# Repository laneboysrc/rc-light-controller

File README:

This project is for a light controller for Radio Controlled cars. 

See http://laneboysrc.blogspot.sg/2012/07/diy-car-light-controller-for-3-channel.html
for details.

It makes uses of a PIC 16F628A microcontroller. Firmware and schematics in
Eagle format are included.

To compile you need:
- GNU Make
- gputils (Version 1.0.0; http://gputils.sourceforge.net/)

Also heck out http://laneboysrc.blogspot.sg/2012/12/pre-processor-for-diy-rc-light.html

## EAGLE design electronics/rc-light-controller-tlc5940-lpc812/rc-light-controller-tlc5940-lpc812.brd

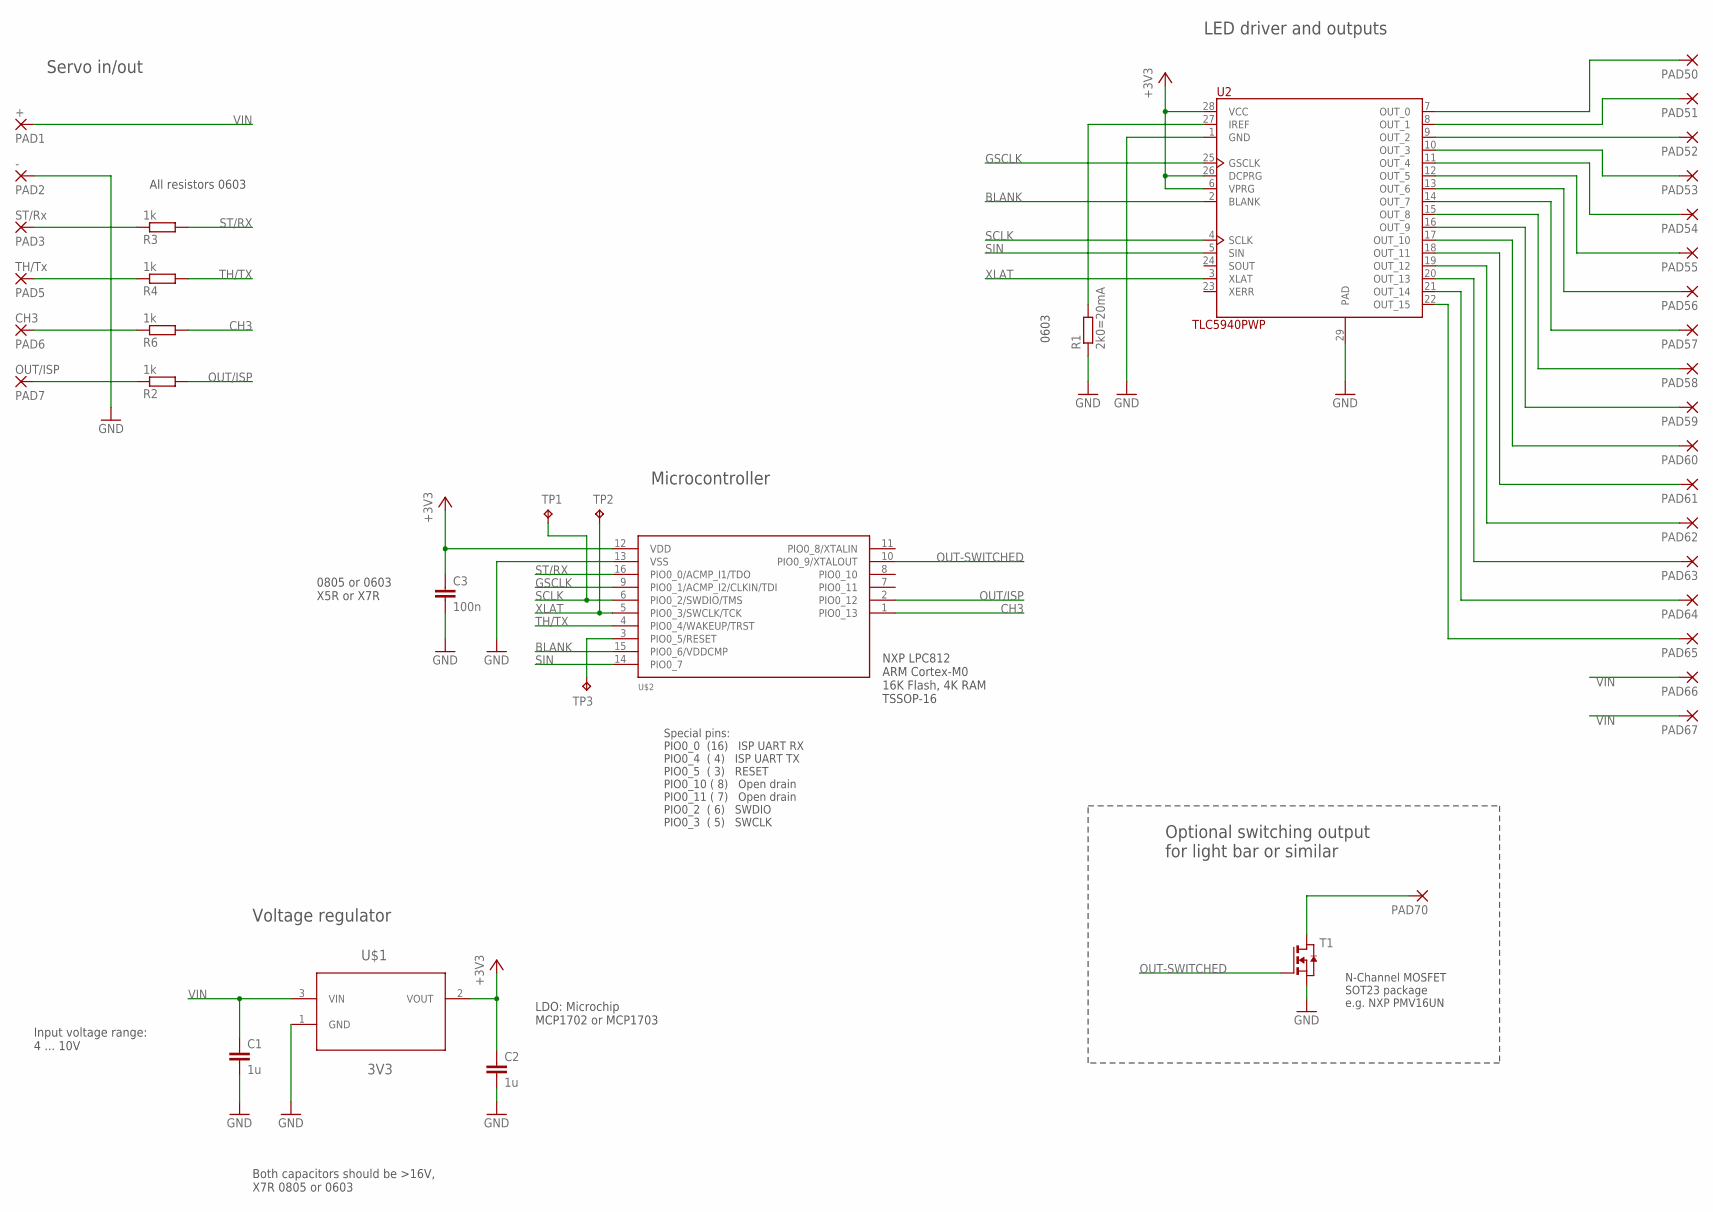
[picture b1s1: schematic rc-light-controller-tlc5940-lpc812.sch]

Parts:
C1, C2: 1u; C0805
C3: 100n; C0805
PAD1: +; SMD80X120
PAD2: -; SMD80X120
PAD3: ST/Rx; SMD80X120
PAD5: TH/Tx; SMD80X120
PAD6: CH3; SMD80X120
PAD7: OUT/ISP; SMD80X120
PAD50, PAD51, PAD52, PAD53, PAD54, PAD55, PAD56, PAD57, PAD58, PAD59, PAD60, PAD61, PAD62, PAD63, PAD64, PAD65, PAD66, PAD67, PAD70: SMD50X100
R1: 2k0=20mA; R0805
R2, R3, R4, R6: 1k; R0603
T1: NMOSSOT23; SOT-23
TP1: SWDIO; TP10R
TP2: SWCLK; TP10R
TP3: RESET; TP10R
U2: TLC5940PWP; SOP65P640X120-29N
U$1: 3V3; SOT95P300X145-3N
U$2: LPC812; TSSOP16

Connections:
+3V3: C2.1, C3.1, U2.6 (VPRG), U2.26 (DCPRG), U2.28 (VCC), U$1.2 (VOUT), U$2.12 (VDD)
BLANK: U2.2 (BLANK), U$2.15 (PIO0_6/VDDCMP)
CH3: R6.2, U$2.1 (PIO0_13)
GND: C1.2, C2.2, C3.2, PAD2.1, R1.1, T1.2 (S), U2.1 (GND), U2.29 (PAD), U$1.1 (GND), U$2.13 (VSS)
GSCLK: U2.25 (GSCLK), U$2.9 (PIO0_1/ACMP_I2/CLKIN/TDI)
IREF: R1.2, U2.27 (IREF)
unnamed: PAD6.1, R6.1
unnamed: PAD70.1, T1.1 (D)
unnamed: TP3.TP, U$2.3 (PIO0_5/RESET)
unnamed: PAD7.1, R2.1
unnamed: PAD3.1, R3.1
unnamed: PAD5.1, R4.1
OUT0: PAD50.1, U2.7 (OUT_0)
OUT1: PAD51.1, U2.8 (OUT_1)
OUT2: PAD52.1, U2.9 (OUT_2)
OUT3: PAD53.1, U2.10 (OUT_3)
OUT4: PAD54.1, U2.11 (OUT_4)
OUT5: PAD55.1, U2.12 (OUT_5)
OUT6: PAD56.1, U2.13 (OUT_6)
OUT7: PAD57.1, U2.14 (OUT_7)
OUT8: PAD58.1, U2.15 (OUT_8)
OUT9: PAD59.1, U2.16 (OUT_9)
OUT10: PAD60.1, U2.17 (OUT_10)
OUT11: PAD61.1, U2.18 (OUT_11)
OUT12: PAD62.1, U2.19 (OUT_12)
OUT13: PAD63.1, U2.20 (OUT_13)
OUT14: PAD64.1, U2.21 (OUT_14)
OUT15: PAD65.1, U2.22 (OUT_15)
OUT-SWITCHED: T1.3 (G), U$2.10 (PIO0_9/XTALOUT)
OUT/ISP: R2.2, U$2.2 (PIO0_12)
SCLK: TP1.TP, U2.4 (SCLK), U$2.6 (PIO0_2/SWDIO/TMS)
SIN: U2.5 (SIN), U$2.14 (PIO0_7)
ST/RX: R3.2, U$2.16 (PIO0_0/ACMP_I1/TDO)
TH/TX: R4.2, U$2.4 (PIO0_4/WAKEUP/TRST)
VIN: C1.1, PAD1.1, PAD66.1, PAD67.1, U$1.3 (VIN)
XLAT: TP2.TP, U2.3 (XLAT), U$2.5 (PIO0_3/SWCLK/TCK)

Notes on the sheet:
0603
Special pins: PIO0_0 (16) ISP UART RX PIO0_4 ( 4) ISP UART TX PIO0_5 ( 3) RESET PIO0_10 ( 8) Open drain PIO0_11 ( 7) Open drain PIO0_2 ( 6) SWDIO PIO0_3 ( 5) SWCLK
Servo in/out
LED driver and outputs
Voltage regulator
Microcontroller
Both capacitors should be >16V, X7R 0805 or 0603
All resistors 0603
Input voltage range: 4 ... 10V
LDO: Microchip MCP1702 or MCP1703
0805 or 0603 X5R or X7R
NXP LPC812 ARM Cortex-M0 16K Flash, 4K RAM TSSOP-16
Optional switching output for light bar or similar
N-Channel MOSFET SOT23 package e.g. NXP PMV16UN

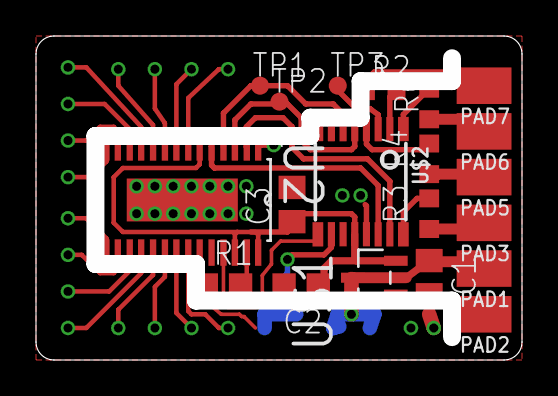
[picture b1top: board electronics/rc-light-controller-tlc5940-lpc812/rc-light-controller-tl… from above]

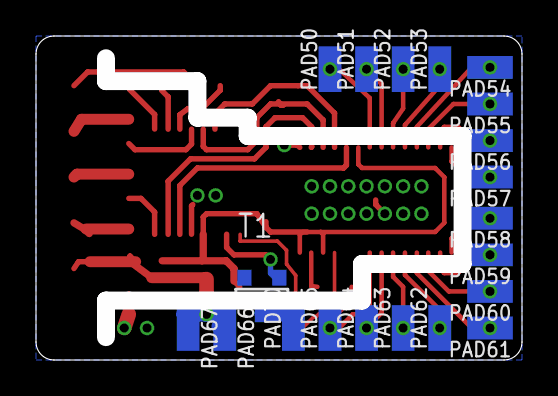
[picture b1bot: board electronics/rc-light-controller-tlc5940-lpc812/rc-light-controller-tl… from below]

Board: 2 copper layers, 26.0 x 17.0 mm, 40 parts (20 on the bottom side), 36 nets.

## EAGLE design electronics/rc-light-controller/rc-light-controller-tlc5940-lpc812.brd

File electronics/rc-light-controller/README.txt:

rc-light-controller-tlc5940-smd.sch and rc-light-controller-tlc5940-smd.brd
are correct and have been actually manufactured already. One directory
up contains Gerber files for the board.

Note: the PCB in rc-light-controller.brd is not for production, it is for
reference to build it on a protoyping board only.
rc-light-controller-tlc5940.sch is not updated and should not be used.

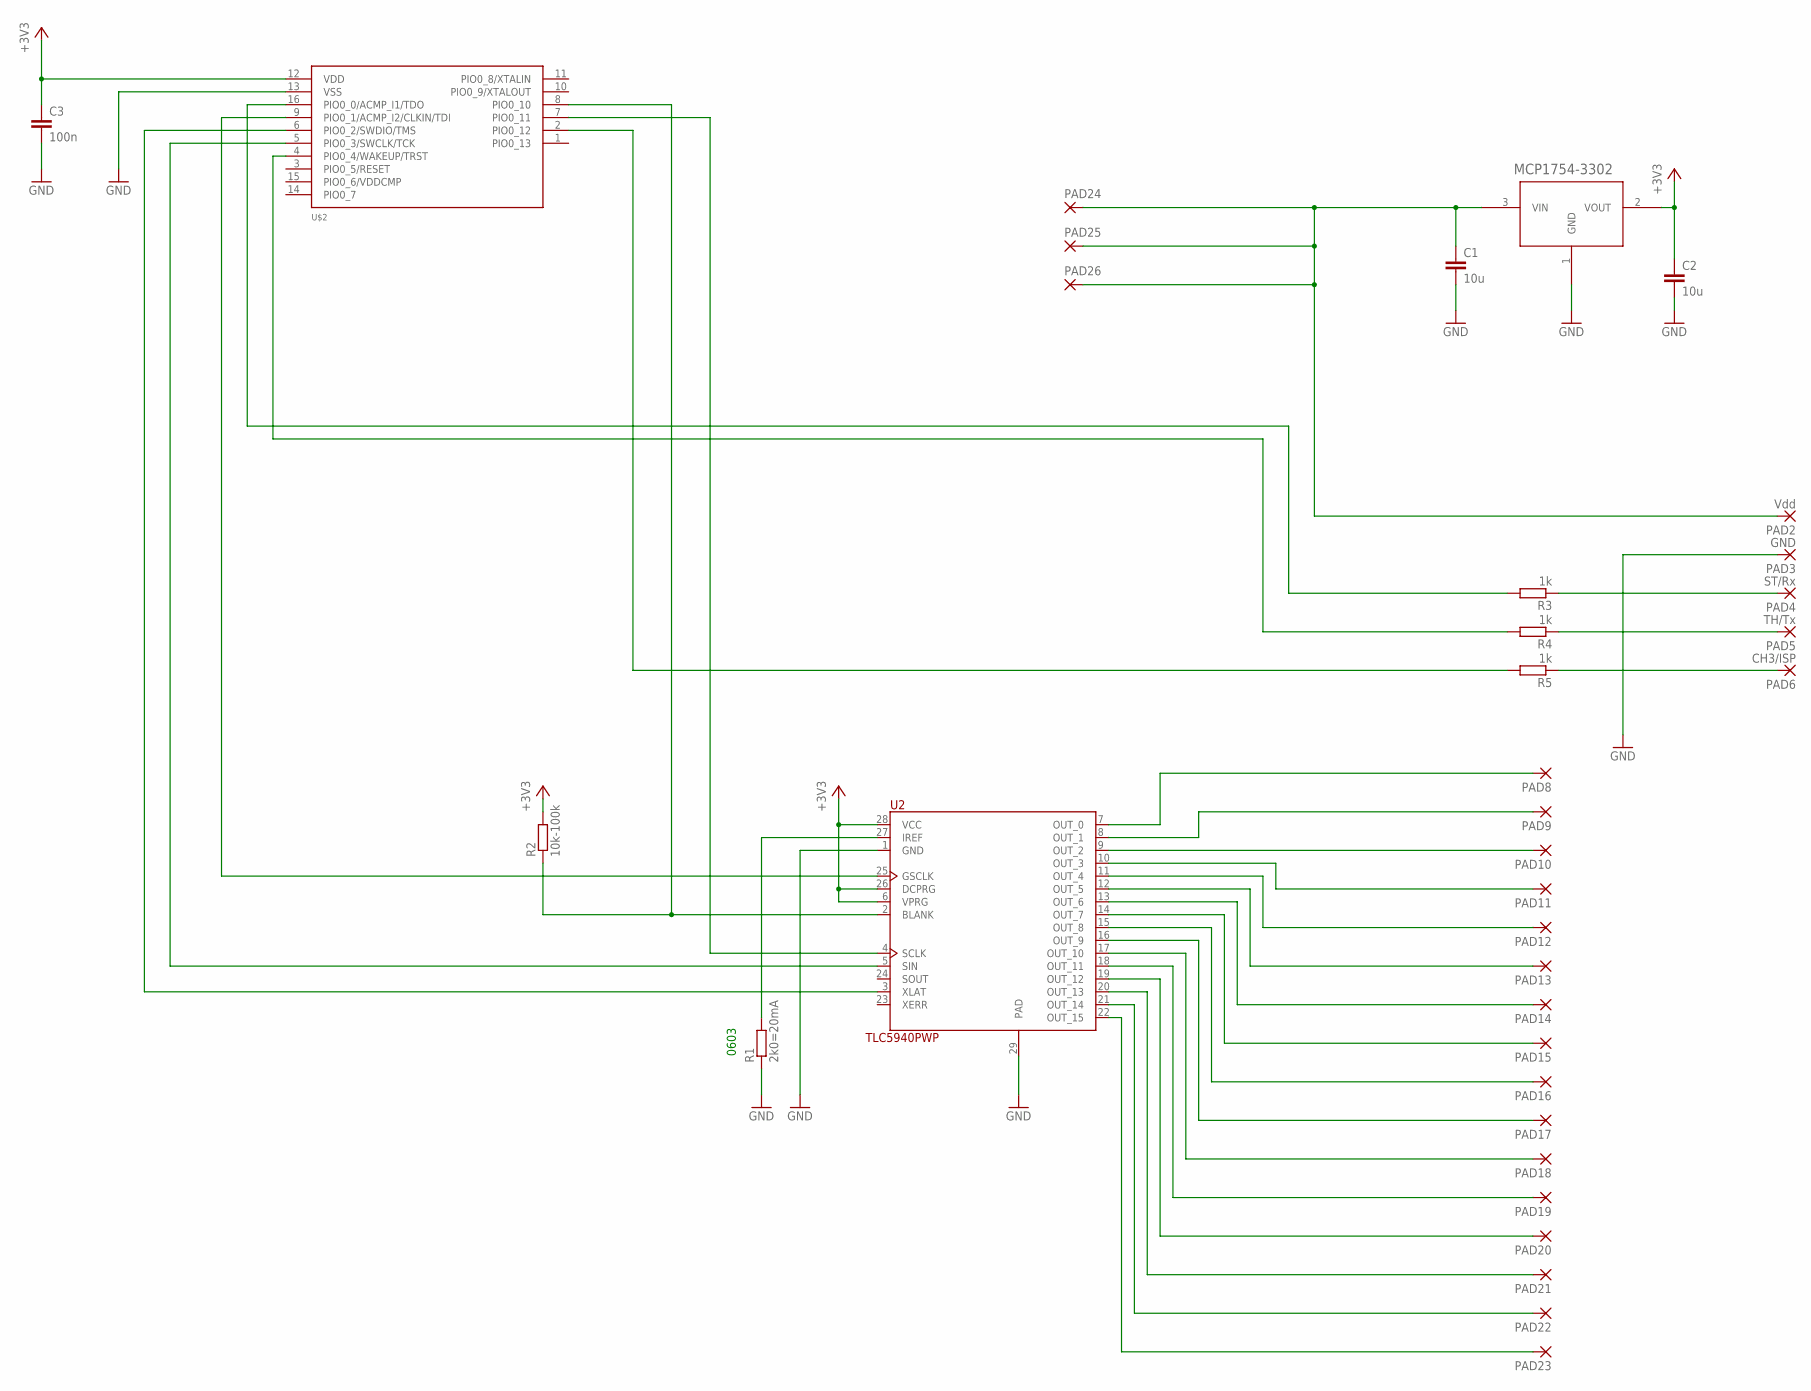
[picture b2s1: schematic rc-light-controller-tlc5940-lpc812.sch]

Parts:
C1, C2: 10u; C0805
C3: 100n; C0805
PAD2: Vdd; SMD80X120
PAD3: GND; SMD80X120
PAD4: ST/Rx; SMD80X120
PAD5: TH/Tx; SMD80X120
PAD6: CH3/ISP; SMD80X120
PAD8, PAD9, PAD10, PAD11, PAD12, PAD13, PAD14, PAD15, PAD16, PAD17, PAD18, PAD19, PAD20, PAD21, PAD22, PAD23, PAD24, PAD25, PAD26: SMD50X100
R1: 2k0=20mA; R0805
R2: 10k-100k; R0805
R3, R4, R5: 1k; R0805
U2: TLC5940PWP; SOP65P640X120-29N
U$1: MCP1754X-XXXXX/C; SOT-23A_MC
U$2: LPC812; TSSOP16

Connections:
BLANK: R2.1, U2.2 (BLANK), U$2.8 (PIO0_10)
GND: C1.2, C2.2, C3.2, PAD3.1, R1.1, U2.1 (GND), U2.29 (PAD), U$1.1 (GND), U$2.13 (VSS); also elsewhere on the board
GSCLK: U2.25 (GSCLK), U$2.9 (PIO0_1/ACMP_I2/CLKIN/TDI)
IREF: R1.2, U2.27 (IREF)
unnamed 5: U$2.1 (PIO0_13); also elsewhere on the board
unnamed 7: U$2.10 (PIO0_9/XTALOUT); also elsewhere on the board
unnamed: PAD4.1, R3.1
unnamed: PAD5.1, R4.1
OUT0: PAD8.1, U2.7 (OUT_0)
OUT1: PAD9.1, U2.8 (OUT_1)
OUT2: PAD10.1, U2.9 (OUT_2)
OUT3: PAD11.1, U2.10 (OUT_3)
OUT4: PAD12.1, U2.11 (OUT_4)
OUT5: PAD13.1, U2.12 (OUT_5)
OUT6: PAD14.1, U2.13 (OUT_6)
OUT7: PAD15.1, U2.14 (OUT_7)
OUT8: PAD16.1, U2.15 (OUT_8)
OUT9: PAD17.1, U2.16 (OUT_9)
OUT10: PAD18.1, U2.17 (OUT_10)
OUT11: PAD19.1, U2.18 (OUT_11)
OUT12: PAD20.1, U2.19 (OUT_12)
OUT13: PAD21.1, U2.20 (OUT_13)
OUT14: PAD22.1, U2.21 (OUT_14)
OUT15: PAD23.1, U2.22 (OUT_15)
SCLK: U2.4 (SCLK), U$2.7 (PIO0_11)
SIN: U2.5 (SIN), U$2.5 (PIO0_3/SWCLK/TCK)
SLAT: U2.3 (XLAT), U$2.6 (PIO0_2/SWDIO/TMS)
ST/CLK/RX: R4.2, U$2.4 (PIO0_4/WAKEUP/TRST)
TH/DAT/TX: R3.2, U$2.16 (PIO0_0/ACMP_I1/TDO)
VIN: C1.1, PAD2.1, PAD24.1, PAD25.1, PAD26.1, U$1.3 (VIN); also elsewhere on the board

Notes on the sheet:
0603

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
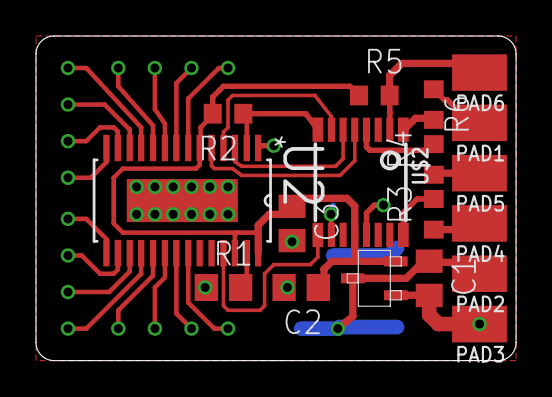
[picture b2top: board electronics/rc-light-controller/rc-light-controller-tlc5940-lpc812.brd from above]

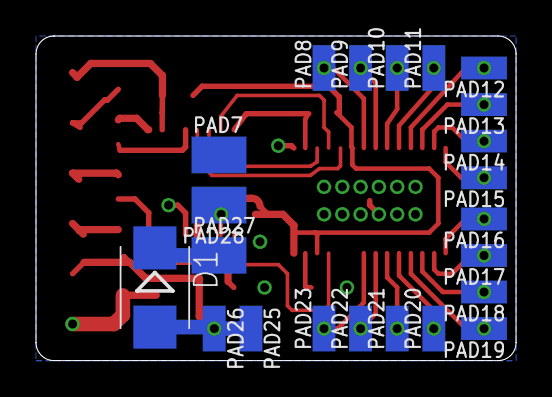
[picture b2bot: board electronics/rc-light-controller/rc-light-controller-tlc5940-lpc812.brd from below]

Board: 2 copper layers, 26.7 x 18.0 mm, 40 parts (22 on the bottom side), 34 nets.

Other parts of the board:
D1: (Diode); SMB
PAD1: CH3; SMD80X120
PAD7: GND; SMD80X120
PAD27: +5V; SMD80X120
PAD28: Data out; SMD80X120
R6: 1k; R0603

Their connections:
GND: PAD7.1; also elsewhere on the board
unnamed: PAD1.1, R6.1
unnamed 5: R6.2; also elsewhere on the board
unnamed: D1.C, PAD27.1
unnamed 7: PAD28.1; also elsewhere on the board
VIN: D1.A; also elsewhere on the board

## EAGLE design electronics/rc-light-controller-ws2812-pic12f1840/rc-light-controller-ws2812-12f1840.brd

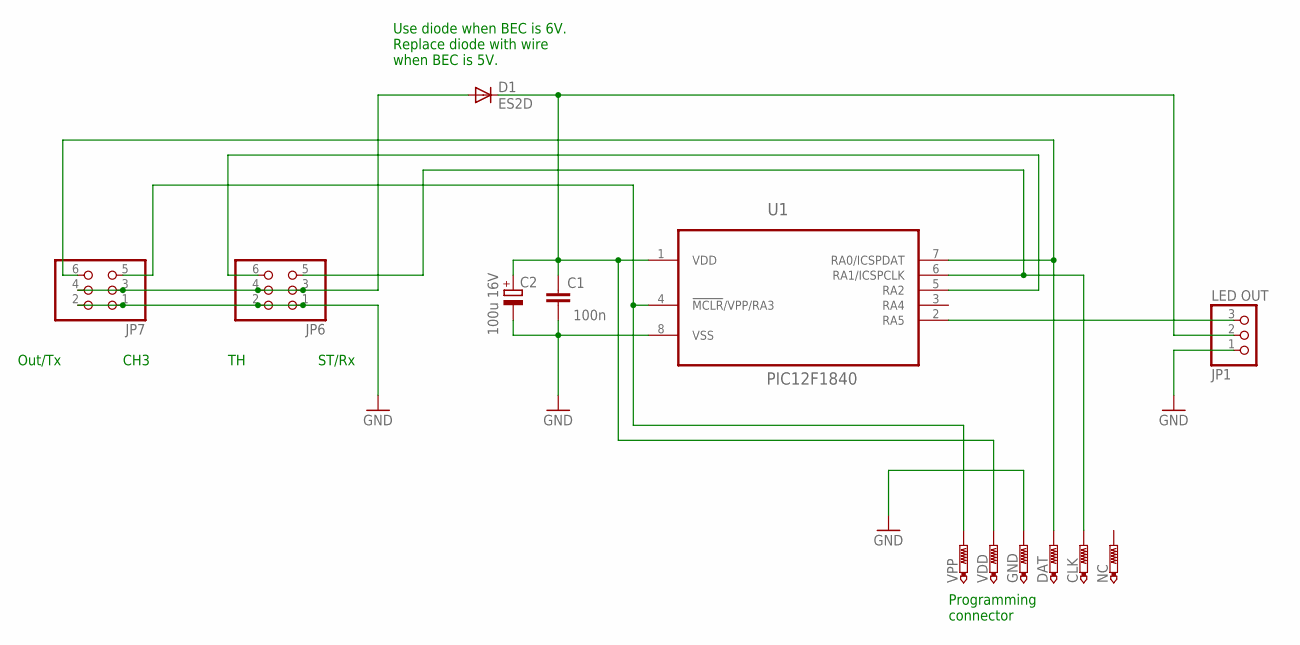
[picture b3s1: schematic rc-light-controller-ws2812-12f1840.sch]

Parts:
C1: 100n; C0805K
C2: 100u 16V; 153CLV-0605
CLK: PTR1TP14R; TP14R
D1: ES2D; SMB
DAT: PTR1TP14R; TP14R
GND: PTR1TP14R; TP14R
JP1: LED OUT; 1X03
JP6, JP7: PINHD-2X3; 2X03
NC: PTR1TP14R; TP14R
U1: 12F1840; SOIC127P600X175-8N
VDD: PTR1TP14R; TP14R
VPP: PTR1TP14SQ; TP14SQ

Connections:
CH3: JP7.5, U1.4 (!MCLR!/VPP/RA3), VPP.TP
GND: C1.2, C2.-, GND.TP, JP1.1, JP6.1, JP6.2, JP7.1, JP7.2, U1.8 (VSS)
unnamed: JP1.3, U1.2 (RA5)
OUT/TX: DAT.TP, JP7.6, U1.7 (RA0/ICSPDAT)
ST/RX: CLK.TP, JP6.5, U1.6 (RA1/ICSPCLK)
TH: JP6.6, U1.5 (RA2)
VBAT: D1.A, JP6.3, JP6.4, JP7.3, JP7.4
VDD: C1.1, C2.+, D1.C, JP1.2, U1.1 (VDD), VDD.TP

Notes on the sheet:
Use diode when BEC is 6V. Replace diode with wire when BEC is 5V.
Programming connector
Out/Tx
CH3
ST/Rx

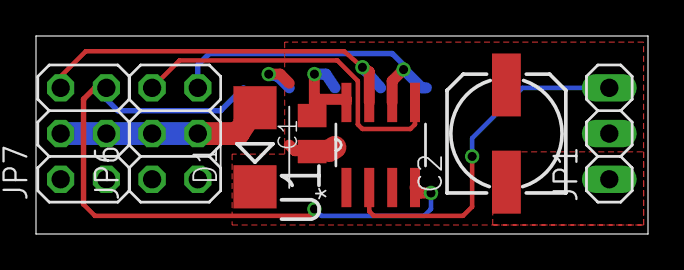
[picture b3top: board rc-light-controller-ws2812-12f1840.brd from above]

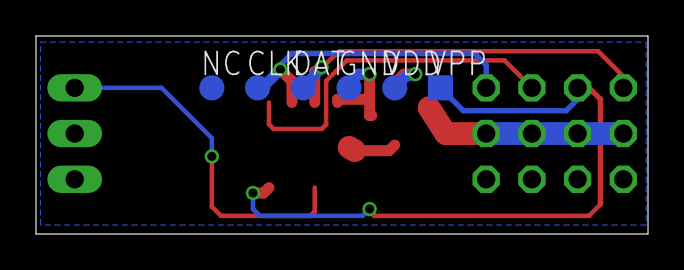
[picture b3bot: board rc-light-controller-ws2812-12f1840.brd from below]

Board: 2 copper layers, 34.0 x 11.0 mm, 13 parts (6 on the bottom side), 8 nets.

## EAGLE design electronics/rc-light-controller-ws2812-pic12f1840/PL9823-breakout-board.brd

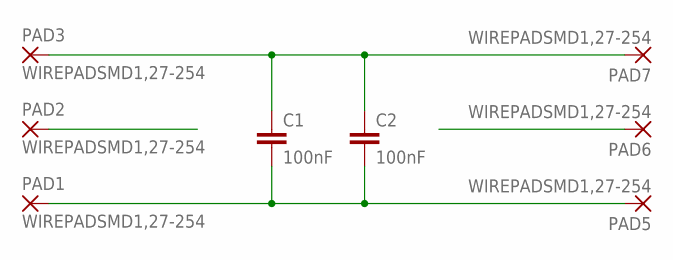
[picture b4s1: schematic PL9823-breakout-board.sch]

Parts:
C1, C2: 100nF; C0805K
PAD1, PAD2, PAD3, PAD5, PAD6, PAD7: WIREPADSMD1,27-254; SMD1,27-2,54

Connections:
+: C1.1, C2.1, PAD3.1, PAD7.1
-: C1.2, C2.2, PAD1.1, PAD5.1
DI: PAD2.1
DO: PAD6.1

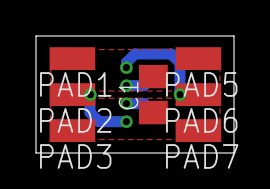
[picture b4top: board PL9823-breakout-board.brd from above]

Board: 2 copper layers, 11.0 x 6.5 mm, 8 parts (1 on the bottom side), 2 nets.

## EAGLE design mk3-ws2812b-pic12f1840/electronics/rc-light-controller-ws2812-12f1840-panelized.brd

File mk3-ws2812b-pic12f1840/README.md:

# Light controller MK3 WS2812b PIC12F1840

The firmware for the MK2 WS2812 PIC12F1840 variant is shared with the [MK2 TLC5940 PIC16F1825 variant](../mk2-tlc5940-pic16f1825/firmware/).

Please consult the [firmware architecture document](../mk2-tlc5940-pic16f1825/doc/firmware-architecture.md) for build instructions and configuration options.

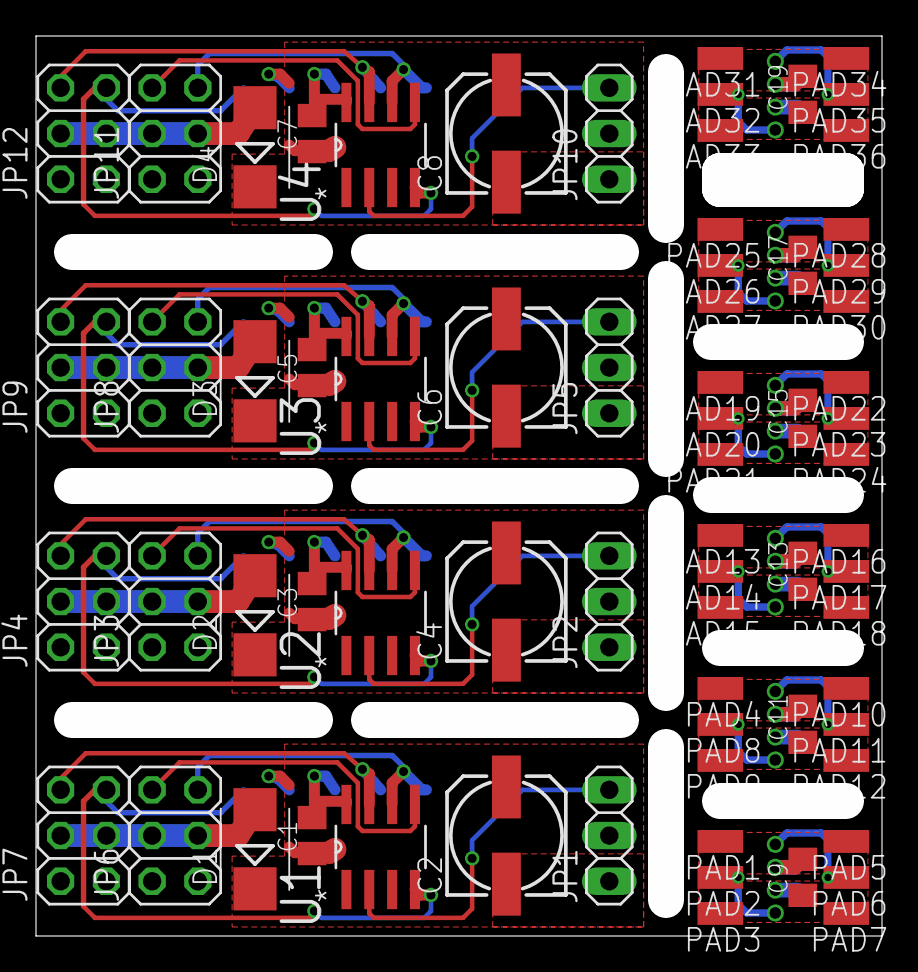
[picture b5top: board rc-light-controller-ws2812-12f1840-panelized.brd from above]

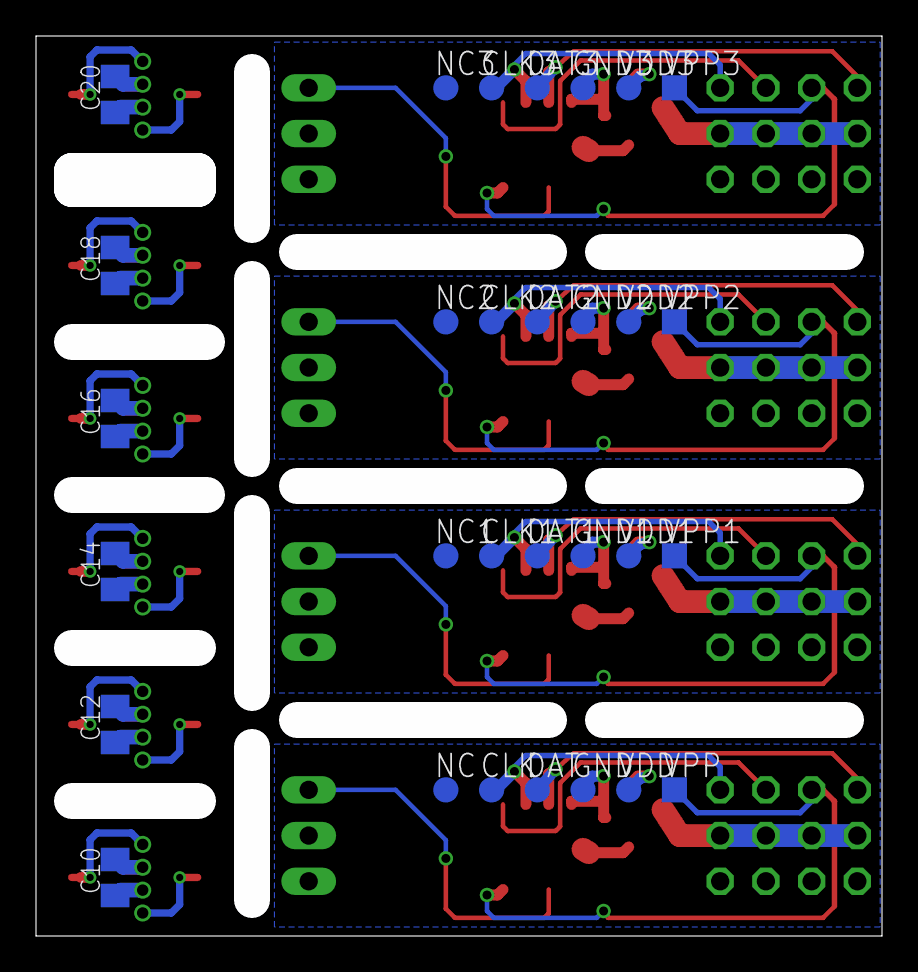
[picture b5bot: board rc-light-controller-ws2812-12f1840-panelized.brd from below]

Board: 2 copper layers, 45.0 x 48.0 mm, 100 parts (30 on the bottom side), 44 nets.

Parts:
C1, C3, C5, C7: 100n; C0805K
C2, C4, C6, C8: 100u 16V; 153CLV-0605
C9, C10, C11, C12, C13, C14, C15, C16, C17, C18, C19, C20: 100nF; C0805K
CLK, CLK1, CLK2, CLK3: PTR1TP14R; TP14R
D1, D2, D3, D4: ES2D; SMB
DAT, DAT1, DAT2, DAT3: PTR1TP14R; TP14R
GND, GND1, GND2, GND3: PTR1TP14R; TP14R
JP1, JP2, JP5, JP10: LED OUT; 1X03
JP3, JP4, JP6, JP7, JP8, JP9, JP11, JP12: 2X03
NC, NC1, NC2, NC3: PTR1TP14R; TP14R
PAD1, PAD2, PAD3, PAD4, PAD5, PAD6, PAD7, PAD8, PAD9, PAD10, PAD11, PAD12, PAD13, PAD14, PAD15, PAD16, PAD17, PAD18, PAD19, PAD20, PAD21, PAD22, PAD23, PAD24, PAD25, PAD26, PAD27, PAD28, PAD29, PAD30, PAD31, PAD32, PAD33, PAD34, PAD35, PAD36: WIREPADSMD1,27-254; SMD1,27-2,54
U1, U2, U3, U4: 12F1840; SOIC127P600X175-8N
VDD, VDD1, VDD2, VDD3: PTR1TP14R; TP14R
VPP, VPP1, VPP2, VPP3: PTR1TP14SQ; TP14SQ

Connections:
+: C9.1, C10.1, PAD3.1, PAD7.1
+1: C11.1, C12.1, PAD9.1, PAD12.1
+2: C13.1, C14.1, PAD15.1, PAD18.1
+3: C15.1, C16.1, PAD21.1, PAD24.1
+4: C17.1, C18.1, PAD27.1, PAD30.1
+5: C19.1, C20.1, PAD33.1, PAD36.1
-: C9.2, C10.2, PAD1.1, PAD5.1
-1: C11.2, C12.2, PAD4.1, PAD10.1
-2: C13.2, C14.2, PAD13.1, PAD16.1
-3: C15.2, C16.2, PAD19.1, PAD22.1
-4: C17.2, C18.2, PAD25.1, PAD28.1
-5: C19.2, C20.2, PAD31.1, PAD34.1
CH1: JP4.5, U2.4, VPP1.TP
CH2: JP9.5, U3.4, VPP2.TP
CH3: JP7.5, U1.4, VPP.TP
CH4: JP12.5, U4.4, VPP3.TP
GND: C1.2, C2.-, GND.TP, JP1.1, JP6.1, JP6.2, JP7.1, JP7.2, U1.8
GND1: C3.2, C4.-, GND1.TP, JP2.1, JP3.1, JP3.2, JP4.1, JP4.2, U2.8
GND2: C5.2, C6.-, GND2.TP, JP5.1, JP8.1, JP8.2, JP9.1, JP9.2, U3.8
GND3: C7.2, C8.-, GND3.TP, JP10.1, JP11.1, JP11.2, JP12.1, JP12.2, U4.8
unnamed: JP2.3, U2.2
unnamed: JP5.3, U3.2
unnamed: JP10.3, U4.2
unnamed: JP1.3, U1.2
OUT/TX: DAT.TP, JP7.6, U1.7
OUT/TX1: DAT1.TP, JP4.6, U2.7
OUT/TX2: DAT2.TP, JP9.6, U3.7
OUT/TX3: DAT3.TP, JP12.6, U4.7
ST/RX: CLK.TP, JP6.5, U1.6
ST/RX1: CLK1.TP, JP3.5, U2.6
ST/RX2: CLK2.TP, JP8.5, U3.6
ST/RX3: CLK3.TP, JP11.5, U4.6
TH: JP6.6, U1.5
TH1: JP3.6, U2.5
TH2: JP8.6, U3.5
TH3: JP11.6, U4.5
VBAT: D1.A, JP6.3, JP6.4, JP7.3, JP7.4
VBAT1: D2.A, JP3.3, JP3.4, JP4.3, JP4.4
VBAT2: D3.A, JP8.3, JP8.4, JP9.3, JP9.4
VBAT3: D4.A, JP11.3, JP11.4, JP12.3, JP12.4
VDD: C1.1, C2.+, D1.C, JP1.2, U1.1, VDD.TP
VDD1: C3.1, C4.+, D2.C, JP2.2, U2.1, VDD1.TP
VDD2: C5.1, C6.+, D3.C, JP5.2, U3.1, VDD2.TP
VDD3: C7.1, C8.+, D4.C, JP10.2, U4.1, VDD3.TP

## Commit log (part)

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2021-05-01 Fix new values when loading old configurations
2021-05-01 Make all example configurations work on latest configurator
    Main issue was labels being called "hazard", which is now
    a built-in variable by default
2021-05-08 Add updated user manual
    - New WebUSB Rev3 photo
    - Move driver info for USB-to-Serial to programming chapter
    - Add "which LEDs" info
2021-05-08 Update TODO
2021-05-09 Add product and LANE Boys RC label
2021-05-09 Rename pre-processor folders
    Instead of multi-aux, we call them 5ch as in the documentation.
    Also stream-line the folder structure of the 3ch and 5ch PP.
2021-05-09 Add 832 label
2021-05-09 Streamline gerber filenames and add schematics PDF everywhere
2021-05-10 Make ground flood go underneath LPC832
2021-05-11 Fix import of old .HEX files
2021-05-12 Add Gerber for LPC832 variants
2021-05-13 Show MCU part number in programming diagnostics
2021-05-13 Add light program that decodes multi-clicks on AUX2
2021-05-13 Improve README
2021-05-15 Adjust cut-out for the case
2021-05-20 Add "upper row is LED+" notice for Mk4P and Mk4S
2021-05-21 Fix 5ch-PP AUX2 for LPC832 variant
2021-05-22 Add German manual for 5ch-PP-S
2021-05-24 Fix PINENABLE for both LPC812 and LPC832
    v39 fixed LPC812, but 832-based Mk4P was no longer working because
    SWD pins are enabled after reset!
2021-05-24 Fix PINENABLE for LPC832l firmware v40
2021-05-26 Add light program that enables reversing lights only when main lights are on
2021-06-12 Web app for the USB-to-Serial adapter using Web Serial API
2021-06-12 Remove power status message
2021-06-12 Add WebSerial Programmer
    Now it is possible to use a standard USB-to-Serial adapter
    to program the light controller without using any 3rd party
    software.
    Works in Google Chrome, Microsoft Edge and Opera.
2021-06-27 Add wiring diagram with separte light bar battery
2021-07-04 Make NO SIGNAL and INITIALIZING mutually exclusive
2021-07-04 Update change history
2021-07-18 Add Gerber for Mk4 LPC832 version (Rev6)
2021-07-20 Add LPC832 circuit board for the Mk4S
2021-07-27 Add LPC832 PCB design for Mk4S-mini
2021-07-27 Refactor electronics version name to match everywhere
    Add LPC832 5ch-PP-S version
2021-08-10 Fix soldermask settings
2021-08-29 Fix shelf queen mode
    Issue with the new diagnstics taking place even when
    shelf queen mode is active.
2021-09-19 Add diagram with separate power supply for LEDs
2021-09-19 Update schematics to reflect green LED being low brightness
2021-09-19 Update with latest configurator
2021-10-02 Fix light program (hazard is now a global variable)
2021-10-02 Add light program that disables servo output at light switch positions
2021-10-07 Fix old light programs use of 'hazard' (now a reseved word)
2021-11-01 Add WebUSB Revision 4 draft, based on motor driver as power switch
2021-11-02 Rename files and tweak the layout around the motor driver
2021-11-03 Improve naming of project specific schematics component library
2021-11-04 Fix setting of SMOD for fast baudrate mode
2021-11-05 Change version number for Rev4 WebUSB version
2021-11-12 Add i-Bus test configurator
2021-11-13 Improve WebUSB documentation; move USB-to-Serial to appendix
2021-11-14 Update i-Bus test version with reduced diagnostics
2021-11-15 Remove unused ignore entries
2021-11-22 Save a few bytes by combining indicator printf calls
2021-11-22 Make print_indicator_state static
2021-11-22 Make on_off_function generic to prepare for shelf queen via AUX
2021-11-23 Light programs can now control the shelf queen mode
2021-11-23 Add WebUSB Rev 4 Gerber
2021-11-23 Improve hazard switching
2021-11-24 Disable car functions in shelf queen mode
2021-11-24 Add info regarding shelf queen mode from light program
2021-11-26 Basic LED name editing works
2021-11-26 Add support for LED names to the light program assembler
2021-11-26 Make led names assemble
2021-11-26 Add tooltip to LED name
2021-11-26 Add history
2021-11-26 Add support for LED names in LED configuration and light programs
2021-11-27 Drag configuration files from file manager to the Configurator window
2021-11-27 Update with configurator supporting drag-and-drop
2021-11-27 Add toast when configuration loaded
2021-11-27 Show toast when loading a configuration
2021-11-27 Remove more obsolete files; fix broken links and clarify things
2021-12-03 Add PCB thickness to Gerber filename
2021-12-07 i-Bus implementation done
2021-12-07 Automatic protocol selection now working
2021-12-07 Add info for i-Bus operating mode
2021-12-07 Make servo, pre-processor and i-bus reader conditionally compilable
2021-12-07 Add i-Bus example data from an actual receiver and fix i-Bus decoder
2021-12-08 Update i-Bus version (merged latest master)
2021-12-18 Update TODO list
2021-12-20 Fix all leds if no LED declared
    If no LED is defined, but an assinment was made to "all leds",
    then an error message was shown without any information what
    the issue was.
    Example:
    run always
    all leds = 100
2021-12-21 Increase firmware version to 50 as first i-Bus version
2021-12-22 Update i-Bus documentation and TODO list
2021-12-22 Add offset for AUX channel mapping in i-Bus mode
2021-12-23 Implement i-Bus channel offset for AUX
2021-12-23 Focus programming button when connecting WebUSB in programming page
2021-12-25 Add LPC832 support
2021-12-28 Add i-Bus to documentation
2021-12-28 Update with latest configurator supporting i-Bus
2022-01-09 Add more info about S.Bus and add packet decoder in Python
2022-01-12 Improve the silkscreen
2022-01-12 Move resistor network and improve tracks
2022-01-12 Add Rev3 gerbers
2022-01-15 Add BOM for WebUSB Programmer Rev4
2022-01-19 Add statement regarding one LED per output (or two in series)
    Suggestion from light controller user!
2022-01-27 Change SBUS inverter MOSFET and pullup after testing
2022-01-29 Cleanup and improvements
2022-01-29 Clean-up and restore config
2022-01-29 Add skeleton for WebSerial based S-Bus simulator
2022-01-29 Improve documentation for S.Bus simulator
2022-01-29 SBUS now working!
2022-01-30 Add a blank favicon directly into the HTML
2022-01-30 Improve grammar; add history entry for S.Bus
2022-02-02 Add instructions for S.Bus support
2022-03-22 Add interior light when car is in neutral light program
2022-03-24 Make C1 on WebUSB 10uF to combat voltage drop when light controller is turned on
2022-04-10 Release S.Bus support
2022-05-03 Improve schematics and layout
2022-05-05 Add Gerber for Mk4 Rev7 with S.Bus support
2022-05-07 Add light program that switches certain lights on AUX2
2022-05-14 Make Mk4 Rev7 S.Bus case fit
2022-05-14 Support channels 3..16 when using S.Bus
2022-06-11 Add light program for hazard indicator on dashboard
2022-06-12 Add S.Bus for Mk4
2022-06-16 Add Mk4 Rev7 images
2022-06-17 Add Mk4 Rev 7 documentation with S.Bus support
2022-06-25 Save a few bytes by using int as loop counter
2022-06-25 Fix HEX can not be saved
2022-06-27 Add UI to disable local push button in 5chPP/i-Bus/S.Bus mode
2022-07-02 Update Mk4 offline package with latest configurator
2022-07-14 Use RXPOL to invert S.Bus UART instead of hardware inverter
2022-07-14 Output correct MCU type in diagnostics
    Refactor from a flag to the variable mcu_type
2022-07-14 WebUSB and WebSerial work on file: protocol now
2022-07-15 Use LPC81x_ISP.py tool with .hex as .bin does not work on Python3
2022-07-15 Update WebUSB and WebSerial stand-alone programmers
2022-07-16 Update configurator with version that works on file: protocol
2022-07-18 Add UI for reading of firmware, read into .hex file
2022-07-18 Describe how the read function works around the WebUSB programmer bug
2022-07-18 Add read HEX function to programmer.html for WebUSB
2022-07-22 Fix loading of same .hex file
2022-08-21 Add diagrams for slave with servo reader
2022-08-29 Improve LED value editing
2022-08-31 Add statement that WebUSB requires Windows 8.1 or newer
2022-11-06 Improve description for Baudrate
2022-11-23 Fix Slave when running at 100000 BAUD
    Issue: the slave must not invert the Rx pin! Only when processing
    S-Bus input do we want to invert the Rx pin.
2022-11-23 Fix Slave with 100000 BAUD
2022-12-31 Fix light program name
2023-02-08 Rename wiring diagrams
2023-02-08 Start to get WS2812 working
2023-02-09 Update WS2811 implememtation, works with WS2812B for now
2023-02-10 Add timing for WS2812B and WS2811
2023-02-15 Make WS2811 work
2023-02-15 Use lookup table and transmiter 16 bits in one go
2023-03-03 Fix AUX values being wrong after starting simulator
    The sliders were kept in their position between invocations,
    but the underlying simulator was always reset to 0, so initially
    the values sent to the light controller did not match the
    slider values until a slider is moved.
2023-03-03 Fix AUX values being wrong after starting simulator
2023-04-30 New lpc81x_isp version that supports LPC824
2023-05-28 WS2811 now works on OUT15S with 470R pull-up
    We basically use the transistor as level shifter, but need to
    deal with an inverted signal
2023-06-09 Code now works with WS2811 and the buffer on OUT/ISP
2023-06-09 Add WS281x info and TODO
2023-06-09 Start on disassembler
2023-06-10 Light programs now work, including assembler/disasm/configurator
2023-06-10 Implement ws2811 output options logic
2023-06-12 Rename configurator output file
2023-06-13 Add documentation, Fix data=0xff/fe issue
2023-06-14 Add documentation skeleton
2023-06-16 Add CSS trick for margin
2023-06-16 Reduce code size and add 3 more AUX channels
    AUX4..6 can only be used in light programs
2023-06-16 Add 4 more AUX to simulator and update docs
2023-06-17 Improve documentation, add images
2023-06-18 Add US style school bus red and yellow flashing light
2023-06-18 Add support for AUX4..6 for i-Bus and S.Bus
2023-06-18 Add WS281x documentation and Configurator
2023-06-18 Add PDF and update README
2023-06-20 Add -fshort-enums to pack enums
    This seems to be already the case anyway, but just in case...
2023-06-21 Add DMA code, not tested
2023-06-22 WS281x driver uses DMA to offload the MCU
2023-08-26 Fix Webserial Programmer
2023-09-03 Add WebUSB Rev5 PCB with USB Type C connector
2023-09-07 Move obsolete stuff to branch named 'obsolete'
2023-10-29 Re-add tools
2023-11-06 Add 5ch PP flash diagram
2023-11-07 Start on advanced 3ch AUX configuration
2023-11-08 Make Advanced 3 channel AUX work
2023-11-08 Increment firmware version number
2023-11-08 Port more tools to Python3
2023-11-09 Fix 3ch PP not setting multi-aux flag despite outputing full packet
2023-11-09 Pre-processor always outputs 5 channels. Advanved CH3 settings
2023-11-16 Add files for Pre-processor programming
2023-12-29 Fix servo setup number of clicks is 8, not 7
2024-01-05 Add configuration that fits TRX4M
2024-01-08 Confirmed working configuration for TRX4m (finally...)
2024-01-09 WS281x: output master LEDs too
2024-03-29 Shrink screw holes for a better fit
2024-03-29 Add light program that turns off lights in neutral, restores when driving
2024-09-09 Fix LED names defined in the table were only working in the first Light program
2024-11-05 Remove WebUSB rev 4 (moved to 'obsolete' branch)
2024-11-06 Start on WebUSB rev6 hardware
2024-12-03 WebUSB rev 6 for production
2025-01-12 Add servo output on Slave controlled by light program on Master
2025-01-12 Update Mk4P README
2025-01-13 Port Mk4S to Kicad6; Improve silkscreen for Mk4P and Mk4S
2025-01-13 Fix layout and pass DRC
2025-01-22 Remove WebUSB Rev 5
2025-01-22 Improve file names, BOM and gerbers
2025-01-30 Add light program for random servo movement
2025-02-04 Make multi-function control use advanced settings two-position switch hysteresis
2025-05-01 Add servo out pulse to configurator
2025-05-01 Add configuable servo output range to firmware
2025-05-01 Add servo out pulse configuration to advanced settings
2025-05-22 Remove files that are not required
2025-05-22 Force Slave output to OUT/ISP on slave
2025-05-22 Implement LED table, seems to work now
2025-05-22 Add multi-slave that can drive up to 3 slaves (64 LEDs)
2025-06-09 Multislave: fix LED features not working for Slave 2 and 3
2025-06-09 Multislave: fix firmware version in history
2025-07-27 Light programs run up to 30 (not 50) statements before suspension
